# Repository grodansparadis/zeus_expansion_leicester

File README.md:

<h1>Zeus Expansion Leicester</h1>

IEEE 802.15.4 add on card with Zeus expansion connector. Fits the 
<a href="http://www.grodansparadis.com/odessa/odessa.html">Odessa</a> module
among other modules.

<hr>

This project is part of the <a href="http://www.vscp.org">VSCP (Very Simple Control Protocol) project</a>. 

<hr>

This project is licensed under the 
<a href="http://creativecommons.org/licenses/by-nc-sa/3.0/">Creative Commons open source license Attribution-NonCommercial-ShareAlike 3.0 Unported</a>. 
Other license options are available by conacting <a href="malto:info@grodansparadis.com">Paradis of the Frog AB</a>

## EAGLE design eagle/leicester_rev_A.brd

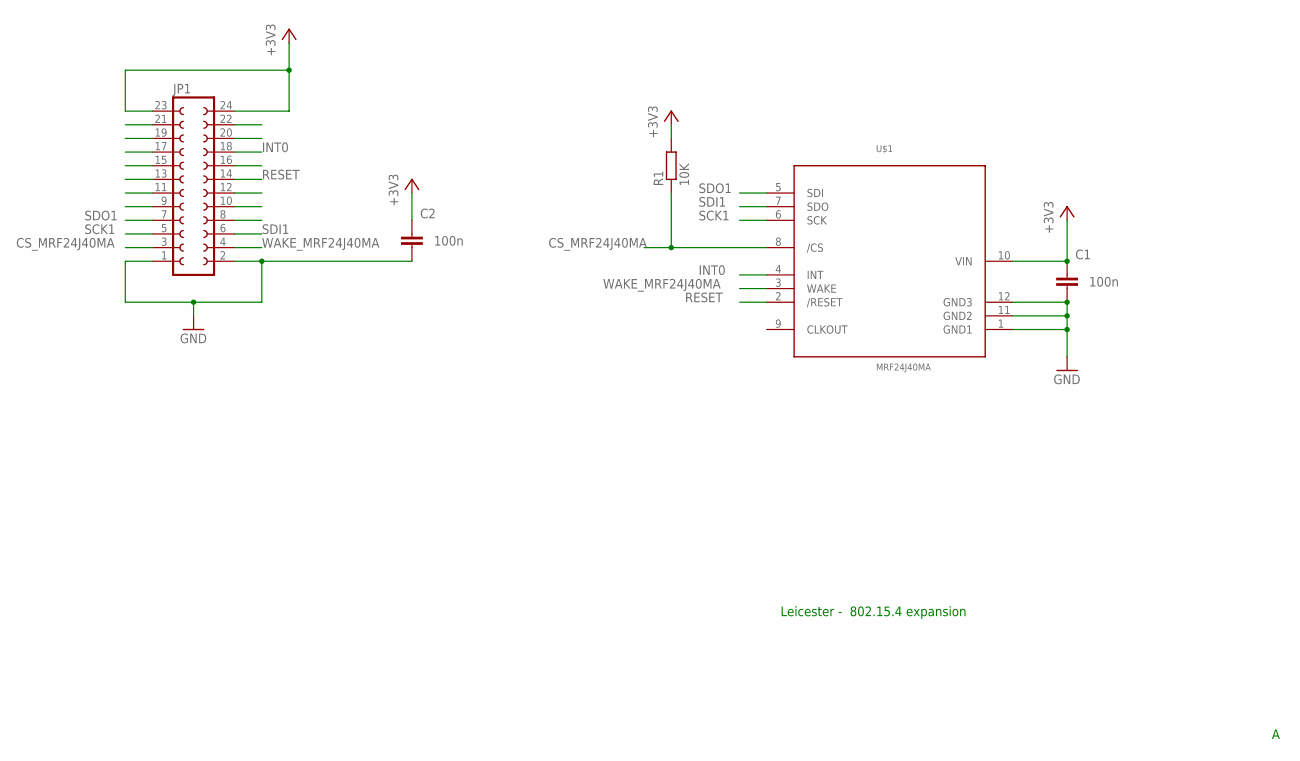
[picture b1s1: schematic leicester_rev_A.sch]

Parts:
C1, C2: 100n; C0805
JP1: FE12-2
R1: 10K; R0805
U$1: MRF24J40MA

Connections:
+3V3: C1.1, C2.1, JP1.23, JP1.24, R1.2, U$1.10 (VIN)
CS_MRF24J40MA: JP1.3, R1.1, U$1.8 (/CS)
GND: C1.2, C2.2, JP1.1, JP1.2, U$1.1 (GND1), U$1.11 (GND2), U$1.12 (GND3)
INT0: JP1.18, U$1.4 (INT)
RESET: JP1.14, U$1.2 (/RESET)
SCK1: JP1.5, U$1.6 (SCK)
SDI1: JP1.6, U$1.7 (SDO)
SDO1: JP1.7, U$1.5 (SDI)
WAKE_MRF24J40MA: JP1.4, U$1.3 (WAKE)

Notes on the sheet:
Leicester - 802.15.4 expansion

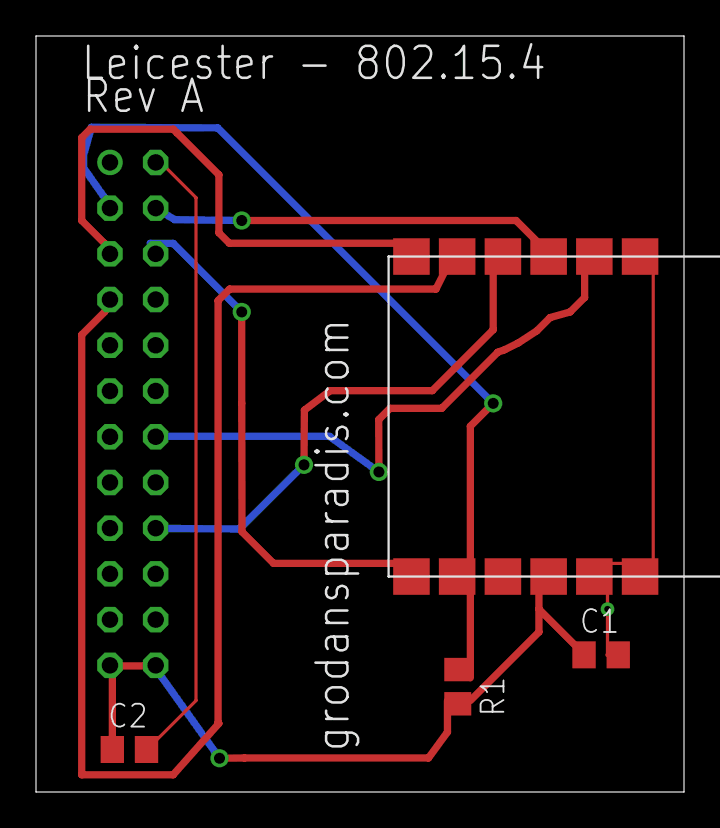
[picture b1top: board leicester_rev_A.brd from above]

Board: 2 copper layers, 36.0 x 42.0 mm, 5 parts (1 on the bottom side), 9 nets.

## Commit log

2015-11-03 Making the design open
2015-12-17 Updated license and readme
